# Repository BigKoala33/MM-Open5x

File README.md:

# MM-Open5x
This repository presents MM-Open5x: a multi-material, multi-axis, open workflow to produce conformal additively manufactured electronics. It is based on [Open5x](https://github.com/FreddieHong19/Open5x).

# License
The contents of this repository is under an MIT License, see [LICENSE.md](https://github.com/FreddieHong19/Open5x/blob/main/LICENSE) for more details.

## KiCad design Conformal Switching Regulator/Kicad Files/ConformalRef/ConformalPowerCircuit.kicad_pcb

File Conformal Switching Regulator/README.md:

# Conformal DC-DC Switching regulator

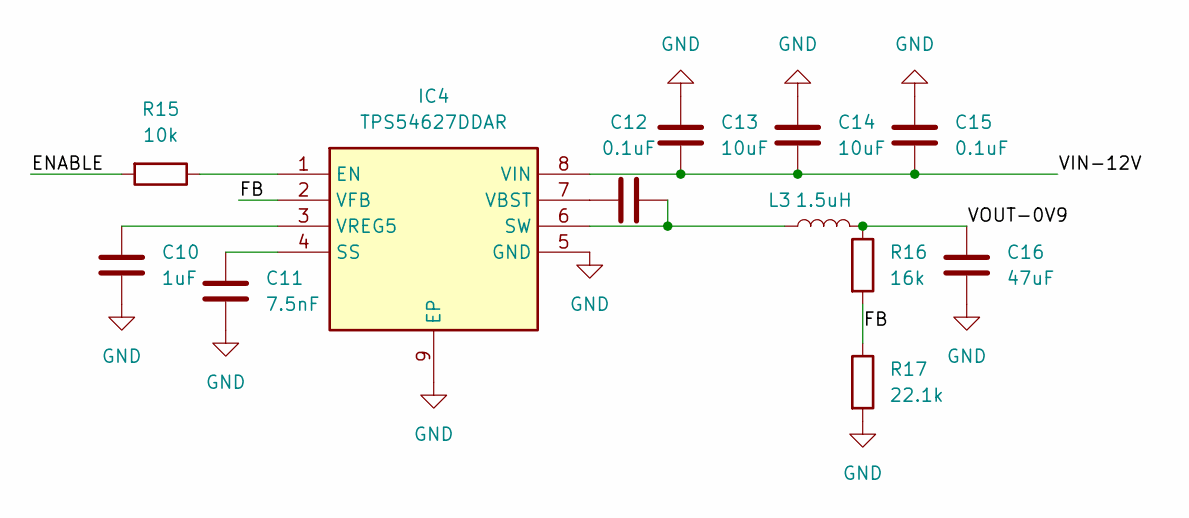
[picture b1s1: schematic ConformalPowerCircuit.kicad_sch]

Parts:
C10: 1uF; C_0603_1608Metric
C11: 7.5nF; C_0603_1608Metric
C12, C15: 0.1uF; C_0603_1608Metric
C13, C14: 10uF; C_1210_3225Metric
C16: 47uF; C_1210_3225Metric
IC4: TPS54627DDAR; SOIC127P600X170-9N; Mouser Part Number 595-TPS54627DDAR
L3: 1.5uH; INDPM6965X240N
R15: 10k; R_0603_1608Metric
R16: 16k; R_0603_1608Metric
R17: 22.1k; R_0603_1608Metric

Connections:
/12VMOTORBW: C13.1, C14.1, C15.1, IC4.8 (VIN)
/BW1EN: R15.2
/BW1_0V9: C16.2, L3.2, R16.1
/FB1: IC4.2 (VFB), R16.2, R17.1
GND: C10.1, C11.1, C13.2, C14.2, C15.2, C16.1, IC4.5 (GND), IC4.9 (EP), R17.2
unnamed: IC4.1 (EN), R15.1
unnamed: C11.2, IC4.4 (SS)
unnamed: C12.2, IC4.6 (SW), L3.1
unnamed: C12.1, IC4.7 (VBST)
unnamed: C10.2, IC4.3 (VREG5)

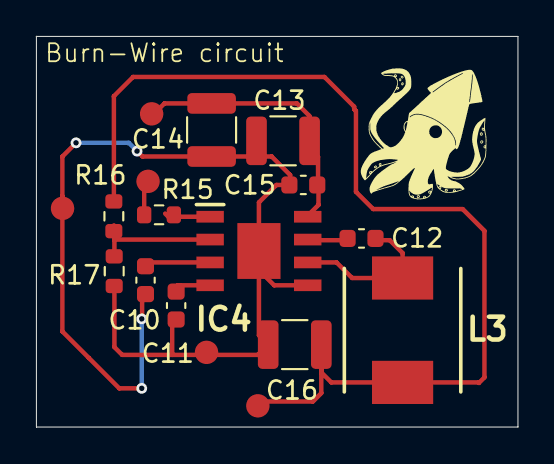
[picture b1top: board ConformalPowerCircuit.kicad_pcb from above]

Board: 2 copper layers, 26.7 x 21.7 mm, 12 parts (0 on the bottom side), 9 nets.

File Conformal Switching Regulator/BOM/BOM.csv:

Reference,Value,Footprint,Qty,MPN
    C10,1uF,0603,1,Generic
    C11,7.5nF,0603,1,Generic
"C12, C15",0.1uF,0603,2,Generic
"C13, C14",10uF,1210,2,Generic
    C16,47uF,1210,1,Generic
    IC4,TPS54627DDAR,SOIC127P600X170-9N,1,TPS54627DDAR
    L3,1.5uH,IHLP2525BDER1R5M01,1,IHLP2525BDER1R5M01
    R15,10k,0603,1,Generic
    R16,16k,0603,1,Generic
    R17,22.1k,0603,1,Generic

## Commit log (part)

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2026-04-23 Rename project from Open5x-Samples to MM-Open5x
2026-04-23 Add README for Conformal S-band Antenna
2026-04-23 Add README for Double curved UWB Antenna
2026-04-23 Rename README.md to README.md
2026-04-23 Add README for Conformal DC-DC Switching Regulator
2026-04-26 Rename Conformal S-band Antenna/SBand-Design.3dm to Conformal S-band Antenna/Design 3D model/SBand-Design.3dm
2026-04-26 Rename Conformal S-band Antenna/S-band-with-Pathing.3dm to Conformal S-band Antenna/3D model with pathing /S-band-with-Pathing.3dm
2026-04-26 Rename UWB-Design.stp to Double curved UWB antenna/Design 3D model/UWB-Design.stp
2026-04-26 Rename UWB-Design.stl to Double curved UWB antenna /Design 3D model /UWB-Design.stl
2026-04-26 Add UWB-Design.stl 3D model file
2026-04-26 Rename UWB-Design.3dm to Double curved UWB antenna/Design 3D model/UWB-Design.3dm
2026-04-26 Rename UWB-with-pathing.3dm to Double curved UWB antenna/3D model with pathing/UWB-with-pathing.3dm
2026-04-28 Update README with project overview
    Add project description for MM-Open5x.
2026-04-28 Fix typo in README.md link to Open5x
2026-05-19 3d mdel w pathing conforma s band
2026-05-19 HFSS sims
2026-05-20 Sband design 3d model update
2026-05-20 Pathing scripts
2026-05-20 3d model and schematic of reg
2026-05-20 Kicad files
